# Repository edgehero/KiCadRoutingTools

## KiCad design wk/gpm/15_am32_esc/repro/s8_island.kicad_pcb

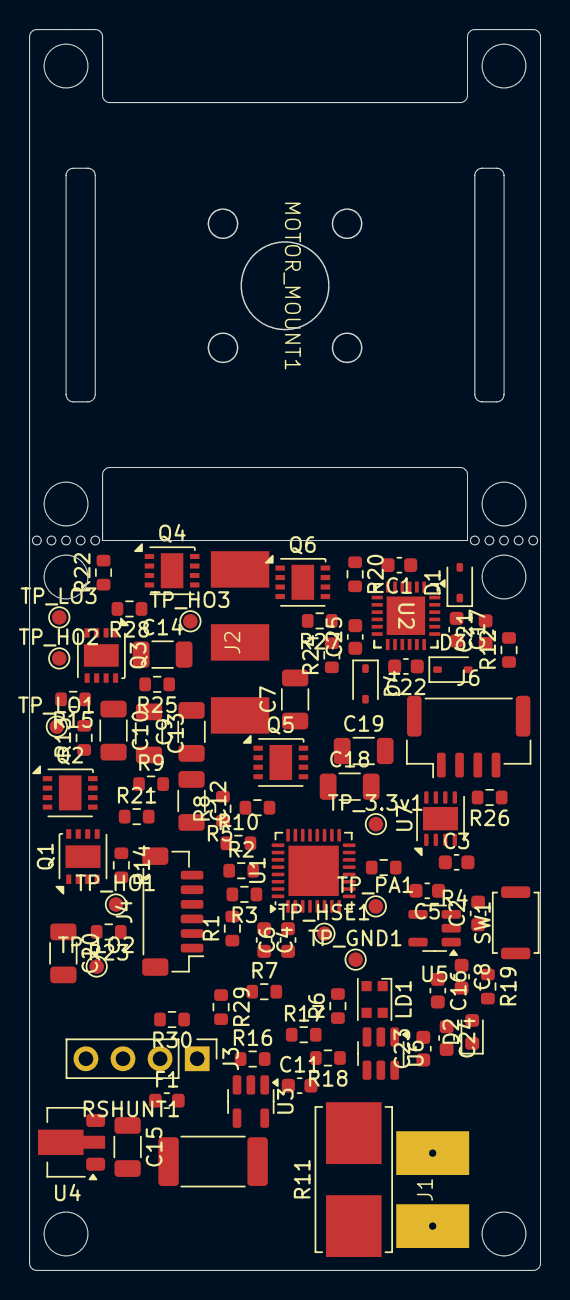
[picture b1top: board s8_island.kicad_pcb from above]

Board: 4 copper layers, 35.0 x 85.0 mm, 93 parts (1 on the bottom side), 55 nets, no tracks yet.

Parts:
C1, C8, C16, C24: 10uF; C_0603_1608Metric
C2, C3, C4, C5, C6, C11, C21, C23: 100nF; C_0603_1608Metric
C7, C9, C10, C12, C13, C14, C15, C18, C19, C20: 22uF; C_1206_3216Metric
C17, C22, C25: 1uF; C_0603_1608Metric
D1, D3, D4: 1N5819WS; D_SOD-323
D2: LED_RED; LED_0603_1608Metric
F1: Fuse; Fuse_0603_1608Metric
J1: NC; 2P_ESC_BAT_PAD_50A_Pitch_5.0mm
J2, J5: NC; 3P_ESC_OUT_50A_5.0mm_Pitch
J3: 2.54mm Pinhead 4P; PinHeader_1x04_P2.54mm_Vertical
J4: SH1.0mm 6P Vertical; JST_SH_BM06B-SRSS-TB_1x06-1MP_P1.00mm_Vertical
J6: GH1.25-4P Vertical; JST_GH_BM04B-GHS-TBT_1x04-1MP_P1.25mm_Vertical
LD1: WS2812B-2020; LED_WS2812B-2020_PLCC4_2.0x2.0mm
MOTOR_MOUNT1: NC; 1404_4300kv_motor
Q1, Q2, Q3, Q4, Q5, Q6: AON7544; DFN-8-1EP_3x3mm_P0.65mm_EP1.55x2.4mm
R1, R5, R8, R18: 30k; R_0603_1608Metric
R2, R6, R9, R17: 3.6k; R_0603_1608Metric
R3, R4, R7, R10, R12, R13, R20, R21, R24, R25, R26: 10k; R_0603_1608Metric
R11: 30A FUSE; Fuseholder_Littelfuse_Nano2_154x
R14, R15, R22, R23, R27, R28, R29, R30: 22R; R_0603_1608Metric
R16: 100k; R_0603_1608Metric
R19: 330R; R_0603_1608Metric
RSHUNT1: 0.3mR 3W; R_2512_6332Metric_Pad1.40x3.35mm_HandSolder
SW1: SW_Push; SW_Push_SPST_NO_Alps_SKRK
TP_3.3v1: NC; TestPoint_Pad_D1.0mm
TP_GND1: NC; TestPoint_Pad_D1.0mm
TP_HO1, TP_HO2, TP_HO3: NC; TestPoint_Pad_D1.0mm
TP_HSE1: NC; TestPoint_Pad_D1.0mm
TP_LO1, TP_LO2, TP_LO3: NC; TestPoint_Pad_D1.0mm
TP_PA1: NC; TestPoint_Pad_D1.0mm
U1: STM32L431KCUx; QFN-32-1EP_5x5mm_P0.5mm_EP3.45x3.45mm
U2: FD6288Q; QFN24_4X4_SEM
U3: INA169; SOT-23-5
U4: HT75xx-1-SOT89; SOT-89-3
U5: AP2112K-3.3; SOT-23-5
U6: SN74LVC1T45DBV; SOT-23-6
U7: TJA1051TK-3; HVSON-8-1EP_3x3mm_P0.65mm_EP1.6x2.4mm

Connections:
3.3v: C4.2, C5.2, C6.2, C16.1, J4.1, R19.1, TP_3.3v1.1, U1.1 (VDD), U1.5 (VDDA), U1.17 (VDD), U5.5 (VOUT), U6.6 (VCCB)
5v: C1.1, C3.1, C8.1, C21.2, C23.2, C24.1, D1.2 (A), D3.2 (A), D4.2 (A), F1.2, J6.1, LD1.4 (VDD), U2.4 (VCC), U5.1 (VIN), U5.3 (EN), U6.1 (VCCA), U7.3 (VCC), U7.5 (VIO)
ADC1_IN6_TEMP: TP_PA1.1, U1.7 (PA1)
ADC1_IN8_BATTERY_CURRENT: R16.2, U1.9 (PA3), U3.1
ADC1_IN11_BATTERY_VOLTAGE: R17.2, R18.2, U1.12 (PA6)
BAT+: C11.1, R11.2, R18.1, RSHUNT1.2, U3.3 (+), U3.5 (V+)
BAT_IN+: J1.1, R11.1
CAN_H: J6.2, U7.7 (CANH)
CAN_L: J6.3, U7.6 (CANL)
CAN_RX: U1.21 (PA11), U7.4 (RXD)
CAN_SILENT: R26.2, U7.8 (S)
CAN_TX: U1.22 (PA12), U7.1 (TXD)
COMP2_INP: R3.1, R7.1, R10.1, U1.27 (PB4)
COMP_INM_A: R1.1, R2.2, R3.2, U1.30 (PB7)
COMP_INM_B: R5.1, R6.2, R7.2, U1.11 (PA5)
COMP_INM_C: R8.1, R9.2, R10.2, U1.10 (PA4)
FD6288_HIN1: U1.20 (PA10), U2.22 (HIN1)
FD6288_HIN2: U1.19 (PA9), U2.23 (HIN2)
FD6288_HIN3: U1.18 (PA8), U2.24 (HIN3)
FD6288_HO1: R12.2, R14.1, U2.19 (HO1)
FD6288_HO2: R20.2, R22.1, U2.16 (HO2)
FD6288_HO3: R24.2, R27.1, U2.13 (HO3)
FD6288_LIN1: U1.15 (PB1), U2.1 (LIN1)
FD6288_LIN2: U1.14 (PB0), U2.2 (LIN2)
FD6288_LIN3: U1.13 (PA7), U2.3 (LIN3)
FD6288_LO1: R13.2, R15.1, U2.11 (LO1)
FD6288_LO2: R21.2, R23.1, U2.10 (LO2)
FD6288_LO3: R25.2, R28.1, U2.9 (LO3)
FD6288_VB1: C17.1, D1.1 (K), U2.20 (VB1)
FD6288_VB2: C22.1, D3.1 (K), U2.17 (VB2)
FD6288_VB3: C25.1, D4.1 (K), U2.14 (VB3)
FD6288_VS1: C17.2, J2.1, J5.1, Q1.1 (S), Q2.3 (D), R1.2, U2.18 (VS1)
FD6288_VS2: C22.2, J2.2, J5.2, Q3.1 (S), Q4.3 (D), R5.2, U2.15 (VS2)
FD6288_VS3: C25.2, J2.3, J5.3, Q5.1 (S), Q6.3 (D), R8.2, U2.12 (VS3)
GND: C1.2, C2.1, C3.2, C4.1, C5.1, C6.1, C7.2, C8.2, C9.2, C10.2, C11.2, C12.2, C13.2, C14.2, C15.2, C16.2, C18.2, C19.2, C20.2, C21.1, C23.1, C24.2, D2.1 (K), J1.2, J3.3, J4.6, J6.4, LD1.2 (VSS), Q2.1 (S), Q4.1 (S), Q6.1 (S), R2.1, R4.1, R6.1, R9.1, R12.1, R13.1, R16.1, R17.1, R20.1, R21.1, R24.1, R25.1, R26.1, SW1.1, TP_GND1.1, U1.16 (VSS), U1.32 (VSS), U1.33 (VSS), U2.6 (COM), U3.2 (GND), U4.1 (GND), U5.2 (GND), U6.2 (GND), U6.5 (DIR), U7.2 (GND), U7.9 (GND)
HSE_IN: TP_HSE1.1, U1.6 (PA0)
unnamed: D2.2 (A), R19.2
unnamed: J3.1, R29.2
unnamed: J3.4, J4.2, R30.2
unnamed: LD1.3 (DIN), U6.3 (A)
unnamed: Q1.2 (G), R14.2, TP_HO1.1
unnamed: Q2.2 (G), R15.2, TP_LO1.1
unnamed: Q3.2 (G), R22.2, TP_HO2.1
unnamed: Q4.2 (G), R23.2, TP_LO2.1
unnamed: Q5.2 (G), R27.2, TP_HO3.1
unnamed: Q6.2 (G), R28.2, TP_LO3.1
unnamed: R4.2, U1.31 (PH3)
unnamed: C15.1, F1.1, U4.3 (VOUT)
ST_NRST: C2.2, SW1.2, U1.4 (NRST)
ST_SWCLK: J4.5, U1.24 (PA14)
ST_SWDIO: J4.4, U1.23 (PA13)
TIM15_CH1: R29.1, U1.8 (PA2)
USART1_TX: R30.1, U1.29 (PB6)
VDD: C7.1, C9.1, C10.1, C12.1, C13.1, C14.1, C18.1, C19.1, C20.1, Q1.3 (D), Q3.3 (D), Q5.3 (D), RSHUNT1.1, U3.4 (-), U4.2 (VIN)
WS2812_SIGNAL: U1.26 (PB3), U6.4 (B)

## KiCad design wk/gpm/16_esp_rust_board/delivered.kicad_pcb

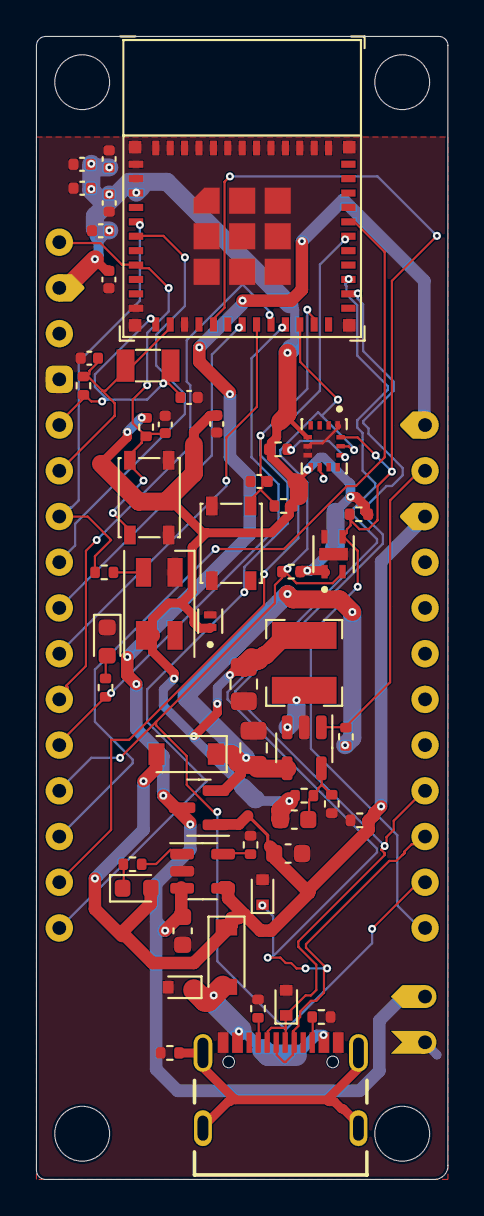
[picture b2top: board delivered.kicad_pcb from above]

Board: 2 copper layers, 22.9 x 63.5 mm, 55 parts (1 on the bottom side), 35 nets.

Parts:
C1, C2, C11: 10nF 10V; C_0402_1005Metric
C3, C4, C9: 100nF 10V; C_0402_1005Metric
C5, C7: 10uF 16V; C_0805_2012Metric
C6: 22pF 50V; C_0603_1608Metric
C8, C10: 1uF 16V; C_0402_1005Metric
C12, C13: DNP; C_0402_1005Metric
C14: 1nF 10V; C_0402_1005Metric
C15, C16: 4.7uF 16V; C_0603_1608Metric
D1: LESD8D3.3CAT5G; SOD-882
D2, D3: LED; LED_0603_1608Metric
D4, D6: B5819W; D_SOD-123
D5, D7, D8: LESD5D5.0CT1G; D_SOD-523
D9: WS2812B; LED_SK6812MINI_PLCC4_3.5x3.5mm_P1.75mm
J1: USB4105-GF-A; GCT_USB4105-GF-A
L1: SPH4018H2R2MT (2.2uH 2.2A); L_Bourns-SRN4018
Q1: DMG3415U; SOT-23
R1, R8, R9, R17, R18, R19: 10kR 1%; R_0402_1005Metric
R2, R15: 100kR 1%; R_0402_1005Metric
R3: 22k1R 1%; R_0402_1005Metric
R4, R6: 5k1R 1%; R_0402_1005Metric
R5, R7, R11: 0R 1%; R_0402_1005Metric
R10: 470R 1%; R_0402_1005Metric
R12: DNP; R_0402_1005Metric
R14: 1kR 1%; R_0402_1005Metric
SW1, SW2: SW_Push; SW_SPST_PTS810
TP2: IMU_INT2; TestPoint_Pad_D1.0mm
U1: SHTC3; SON100P200X200X80-5N
U2: ICM-42670-P; IC_ICM-42670-P
U3: ESP32-C3-MINI-1
U4: Rust_Board
U5: SY8088; SOT-23-5
U6: MCP73831T-2ACI/OT; SOT-23-5
Y1: 32.768Hz; Crystal_SMD_3215-2Pin_3.2x1.5mm

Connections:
+3V3: C1.1, C2.1, C3.1, C4.1, C6.1, C7.1, C8.1, C9.1, C11.1, D1.1 (A1), D9.1 (VDD), L1.2, R2.1, R7.2, R8.1, R17.1, R18.1, R19.1, U1.1 (VDD), U2.5 (VDDIO), U2.8 (VDD), U3.3 (3V3), U4.2 (3V3)
+5V: C5.1, D4.1 (K), Q1.2 (S), R1.1, U5.4 (IN)
+BATT: C16.1, Q1.3 (D), U4.28 (VBAT), U4.30 (BAT+), U6.3 (VBAT)
/Buck_Coil: L1.1, U5.3 (LX)
CHIP_PU: C10.1, R8.2, SW1.1, U3.8 (EN/CHIP_PU), U4.1 (RST)
ENABLE: R1.2, U4.27 (ENABLE), U5.1 (EN)
GND: C1.2, C2.2, C3.2, C4.2, C5.2, C7.2, C8.2, C9.2, C10.2, C11.2, C12.2, C13.2, C14.1, C15.1, C16.2, D1.2 (A2), D2.1 (K), D5.2 (A2), D7.2 (A2), D8.2 (A2), D9.3 (VSS), J1.A1_B12 (GND), J1.B1_A12 (GND), R3.2, R4.2, R5.2, R6.2, R9.1, R15.2, SW1.2, SW2.2, U1.4 (VSS), U1.5 (EXP), U2.1 (AP_SDO/AP_AD0), U2.6 (GND), U2.7 (FSYNC), U3.1 (GND), U3.2 (GND), U3.11 (GND), U3.14 (GND), U3.36 (GND), U4.4 (GND), U4.29 (BAT-), U5.2 (GND), U6.2 (VSS)
IO0: C12.1, R12.1, U3.12 (GPIO0/ADC1_CH0/XTAL_32K_P), U4.5 (A0/GPIO0), Y1.1
IO1: C13.1, R12.2, U3.13 (GPIO1/ADC1_CH1/XTAL_32K_N), U4.6 (A1/GPIO1), Y1.2
IO2: R11.1, U3.5 (GPIO2/ADC1_CH2), U4.7 (A2/GPIO2)
IO3: U3.6 (GPIO3/ADC1_CH3), U4.8 (A3/GPIO3)
IO4: U3.18 (GPIO4/ADC1_CH4), U4.9 (A4/GPIO4)
IO5: U3.19 (GPIO5/ADC2_CH0), U4.10 (A5/GPIO5)
IO6: U3.20 (GPIO6), U4.11 (GPIO6)
IO7: R10.1, U3.21 (GPIO7), U4.12 (GPIO7)
IO8_SCL: R17.2, U1.2 (SCL), U2.13 (AP_SCL/AP_SCLK), U3.22 (GPIO8), U4.13 (GPIO8), U4.18 (SCL/GPIO8)
IO9_BOOT: C14.2, R19.2, SW2.1, U3.23 (GPIO9), U4.16 (BOOT/GPIO9)
IO10_SDA: R18.2, U1.3 (SDA), U2.14 (AP_SDA/AP_SDIO/AP_SDI), U3.16 (GPIO10), U4.17 (SDA/GPIO10)
IO20_RX: U3.30 (GPIO20/U0RXD), U4.15 (RXD/GPIO20)
IO21_TX: U3.31 (GPIO21/U0TXD), U4.14 (TXD/GPIO21)
unnamed: C6.2, R2.2, R3.1, U5.5 (FB)
unnamed: D2.2 (A), R10.2
unnamed: D3.1 (K), R14.2
unnamed: D6.2 (A), D7.1 (A1), J1.A4_B9 (VBUS), J1.B4_A9 (VBUS)
unnamed: D9.4 (DIN), R11.2
unnamed: J1.A5 (CC1), R6.1
unnamed: J1.B5 (CC2), R4.1
unnamed: J1.S1 (SHELL_GND), J1.S2 (SHELL_GND), J1.S3 (SHELL_GND), J1.S4 (SHELL_GND), R5.1
unnamed: R7.1, U2.12 (AP_CS)
unnamed: R9.2, U6.5 (PROG)
unnamed: R14.1, U6.1 (STAT)
unnamed: TP2.1, U2.9 (INT2)
USB_D+: D8.1 (A1), J1.A6 (DP1), J1.B6 (DP2), U3.27 (GPIO19/USB_D+), U4.19 (USB_D+/GPIO19)
USB_D-: D5.1 (A1), J1.A7 (DN1), J1.B7 (DN2), U3.26 (GPIO18/USB_D-), U4.20 (USB_D-/GPIO18)
VBUS: C15.2, D3.2 (A), D4.2 (A), D6.1 (K), Q1.1 (G), R15.1, U4.26 (VBUS), U6.4 (VDD)
